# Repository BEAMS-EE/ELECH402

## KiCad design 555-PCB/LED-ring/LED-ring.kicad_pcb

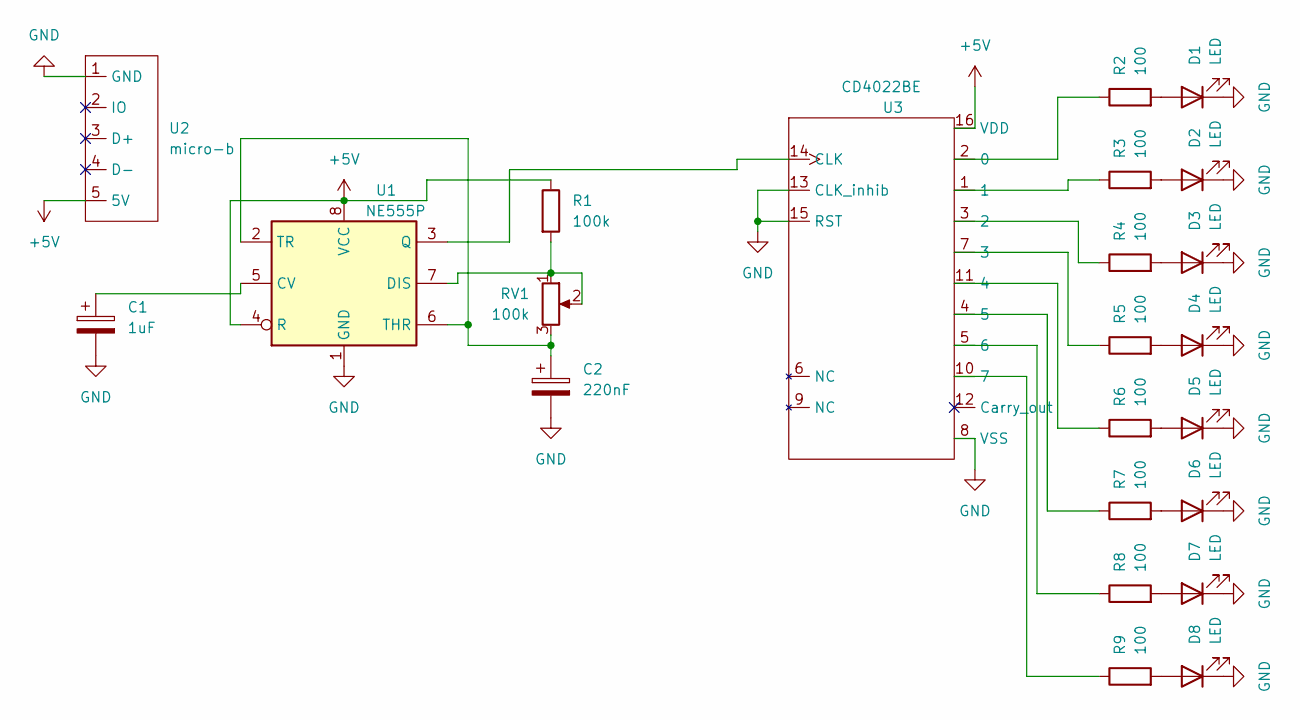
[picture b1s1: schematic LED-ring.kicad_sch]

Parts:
C1: 1uF
C2: 220nF
D1, D2, D3, D4, D5, D6, D7, D8: LED; LED_D5.0mm
R1: 100k
R2, R3, R4, R5, R6, R7, R8, R9: 100; R_Axial_DIN0414_L11.9mm_D4.5mm_P5.08mm_Vertical
RV1: 100k; Potentiometer_Bourns_PTV09A-1_Single_Vertical
U1: NE555P; DIP-8_W7.62mm
U2: micro-b; micro-b_adafruit
U3: CD4022BE

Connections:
+5V: R1.1, U1.4 (R), U1.8 (VCC), U2.5 (5V), U3.16 (VDD)
GND: C1.2, C2.2, D1.1 (K), D2.1 (K), D3.1 (K), D4.1 (K), D5.1 (K), D6.1 (K), D7.1 (K), D8.1 (K), U1.1 (GND), U2.1 (GND), U3.8 (VSS), U3.13 (CLK_inhib), U3.15 (RST)
unnamed: C1.1, U1.5 (CV)
unnamed: C2.1, RV1.3, U1.2 (TR), U1.6 (THR)
unnamed: D1.2 (A), R2.2
unnamed: D2.2 (A), R3.2
unnamed: D3.2 (A), R4.2
unnamed: D4.2 (A), R5.2
unnamed: D5.2 (A), R6.2
unnamed: D6.2 (A), R7.2
unnamed: D7.2 (A), R8.2
unnamed: D8.2 (A), R9.2
unnamed: R1.2, RV1.1, RV1.2, U1.7 (DIS)
unnamed: R2.1, U3.2 (0)
unnamed: R3.1, U3.1
unnamed: R4.1, U3.3 (2)
unnamed: R5.1, U3.7 (3)
unnamed: R6.1, U3.11 (4)
unnamed: R7.1, U3.4 (5)
unnamed: R8.1, U3.5 (6)
unnamed: R9.1, U3.10 (7)
unnamed: U1.3 (Q), U3.14 (CLK)

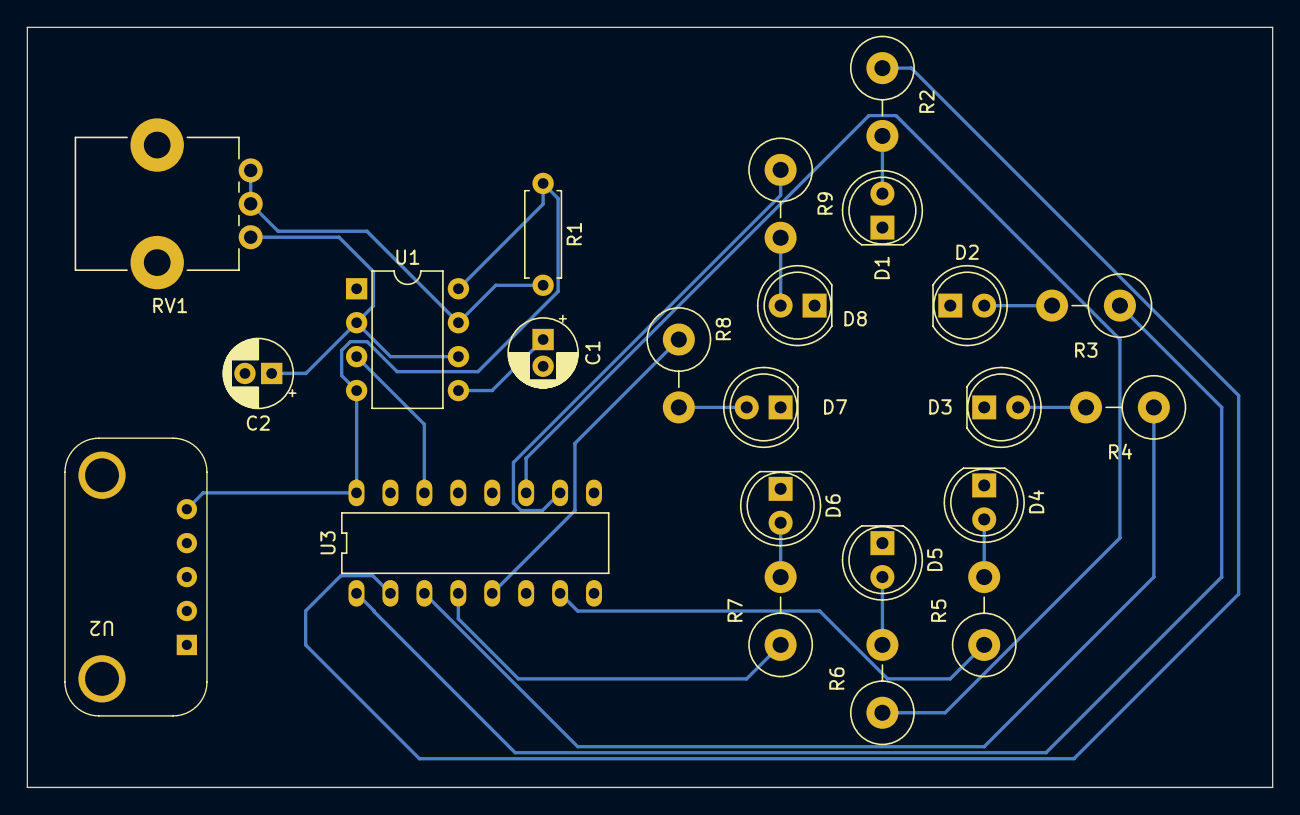
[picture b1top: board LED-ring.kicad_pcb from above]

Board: 2 copper layers, 93.2 x 56.9 mm, 23 parts (0 on the bottom side), 22 nets.

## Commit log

2022-04-26 [Labo PCB] Projet LED ring
2022-11-28 Version 2022-2023
    correction du footprint du USB-breakout
    Ajout de la BoM
2022-11-28 Update de la notice du NE555
2022-11-29 Correction d'une erreur dans le schéma du 555
